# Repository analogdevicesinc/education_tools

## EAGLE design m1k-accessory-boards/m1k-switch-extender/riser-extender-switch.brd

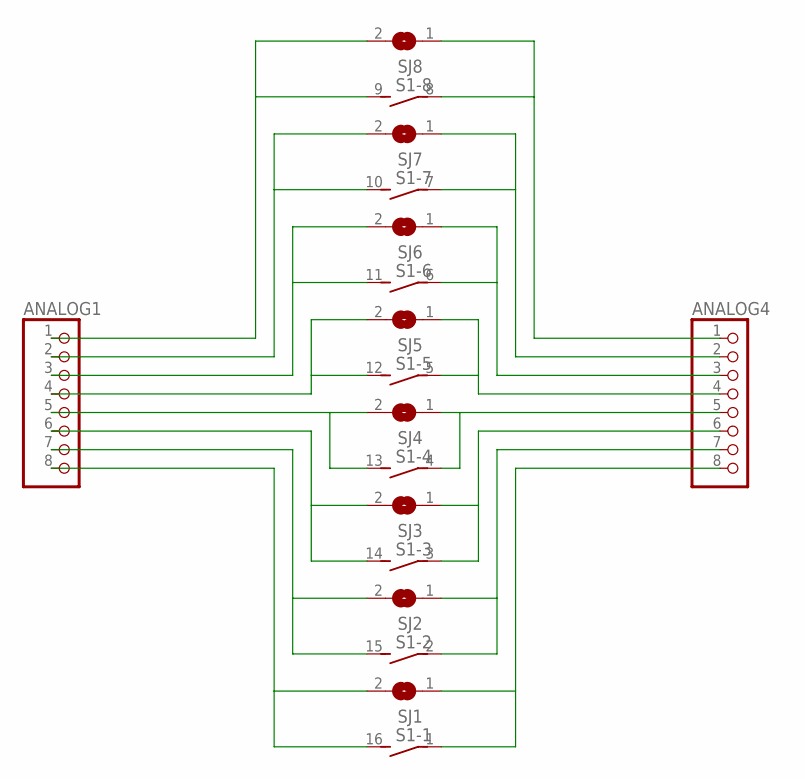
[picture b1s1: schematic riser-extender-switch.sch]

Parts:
ANALOG1, ANALOG4: PINHD-1X8; 1X08
S1: DIP08S
SJ1, SJ2, SJ3, SJ4, SJ5, SJ6, SJ7, SJ8: SJ

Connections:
unnamed: ANALOG1.1, S1.9 (2), SJ8.2
unnamed: ANALOG1.2, S1.10 (2), SJ7.2
unnamed: ANALOG1.3, S1.11 (2), SJ6.2
unnamed: ANALOG1.4, S1.12 (2), SJ5.2
unnamed: ANALOG1.5, S1.13 (2), SJ4.2
unnamed: ANALOG1.6, S1.14 (2), SJ3.2
unnamed: ANALOG1.7, S1.15 (2), SJ2.2
unnamed: ANALOG1.8, S1.16 (2), SJ1.2
unnamed: ANALOG4.5, S1.4 (1), SJ4.1
unnamed: ANALOG4.6, S1.3 (1), SJ3.1
unnamed: ANALOG4.7, S1.2 (1), SJ2.1
unnamed: ANALOG4.8, S1.1, SJ1.1
unnamed: ANALOG4.4, S1.5 (1), SJ5.1
unnamed: ANALOG4.3, S1.6 (1), SJ6.1
unnamed: ANALOG4.2, S1.7 (1), SJ7.1
unnamed: ANALOG4.1, S1.8 (1), SJ8.1

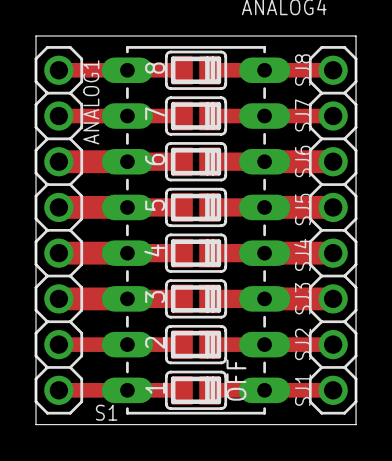
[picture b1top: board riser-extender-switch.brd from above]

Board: 2 copper layers, 17.8 x 21.6 mm, 11 parts (0 on the bottom side), 16 nets.

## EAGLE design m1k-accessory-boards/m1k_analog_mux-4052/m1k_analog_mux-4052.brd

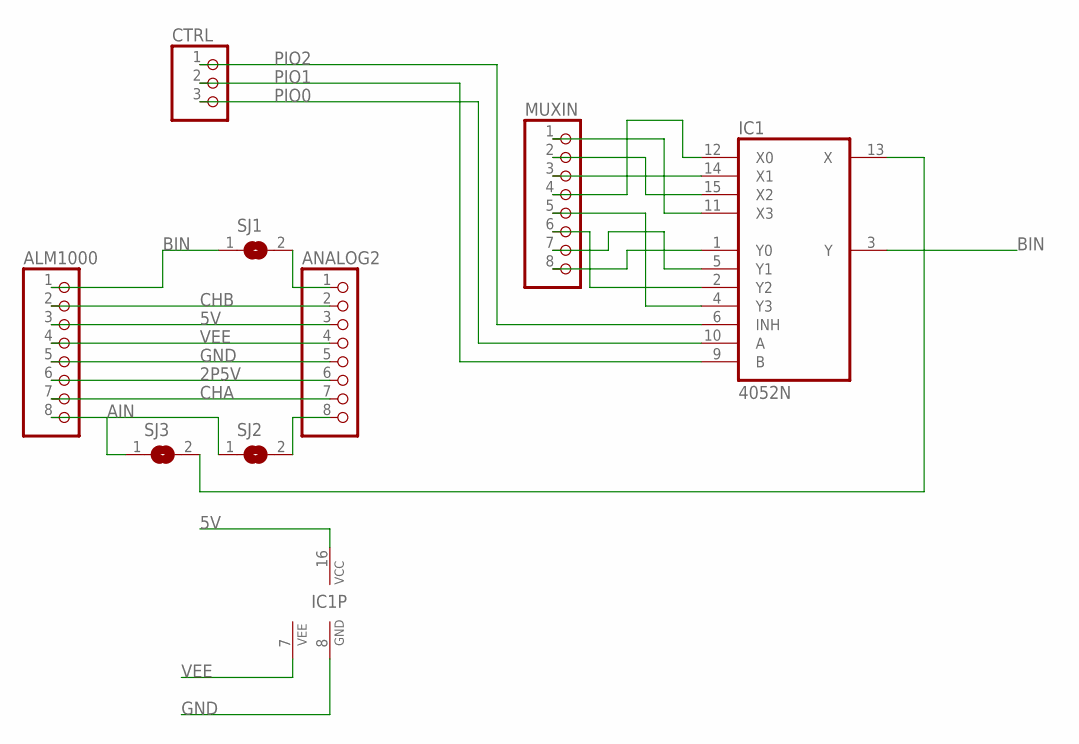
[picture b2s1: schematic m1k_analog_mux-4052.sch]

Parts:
ALM1000: PINHD-1X8; 1X08
ANALOG2: PINHD-1X8; 1X08
CTRL: PINHD-1X3; 1X03
IC1: 4052N; DIL16
MUXIN: PINHD-1X8; 1X08
SJ1, SJ2, SJ3: SJ

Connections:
2P5V: ALM1000.6, ANALOG2.6
5V: ALM1000.3, ANALOG2.3, IC1.16 (VCC)
AIN: ALM1000.8, SJ2.1, SJ3.1
BIN: ALM1000.1, IC1.3 (Y), SJ1.1
CHA: ALM1000.7, ANALOG2.7
CHB: ALM1000.2, ANALOG2.2
GND: ALM1000.5, ANALOG2.5, IC1.8 (GND)
unnamed: IC1.1 (Y0), MUXIN.8
unnamed: ANALOG2.1, SJ1.2
unnamed: IC1.5 (Y1), MUXIN.7
unnamed: IC1.2 (Y2), MUXIN.6
unnamed: IC1.4 (Y3), MUXIN.5
unnamed: IC1.11 (X3), MUXIN.1
unnamed: IC1.15 (X2), MUXIN.2
unnamed: IC1.14 (X1), MUXIN.3
unnamed: IC1.12 (X0), MUXIN.4
unnamed: ANALOG2.8, SJ2.2
unnamed: IC1.13 (X), SJ3.2
PIO0: CTRL.3, IC1.10 (A)
PIO1: CTRL.2, IC1.9 (B)
PIO2: CTRL.1, IC1.6 (INH)
VEE: ALM1000.4, ANALOG2.4, IC1.7 (VEE)

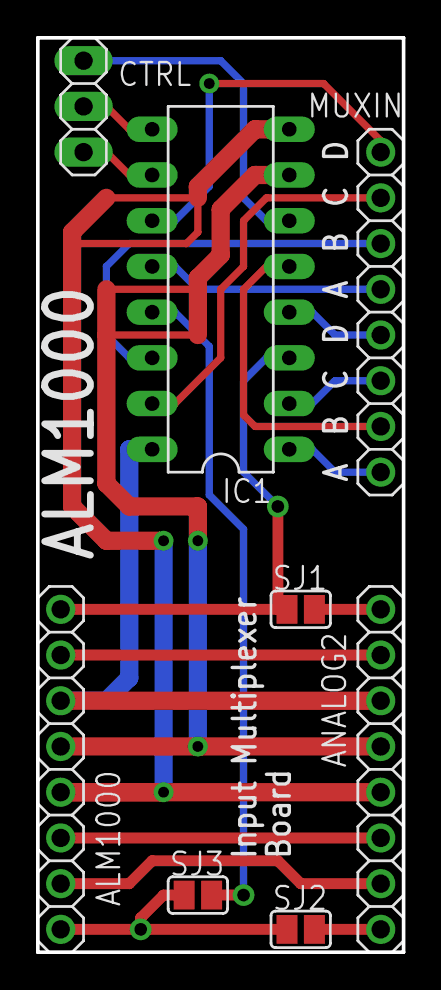
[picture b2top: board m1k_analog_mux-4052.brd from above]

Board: 2 copper layers, 20.3 x 50.8 mm, 8 parts (0 on the bottom side), 22 nets.

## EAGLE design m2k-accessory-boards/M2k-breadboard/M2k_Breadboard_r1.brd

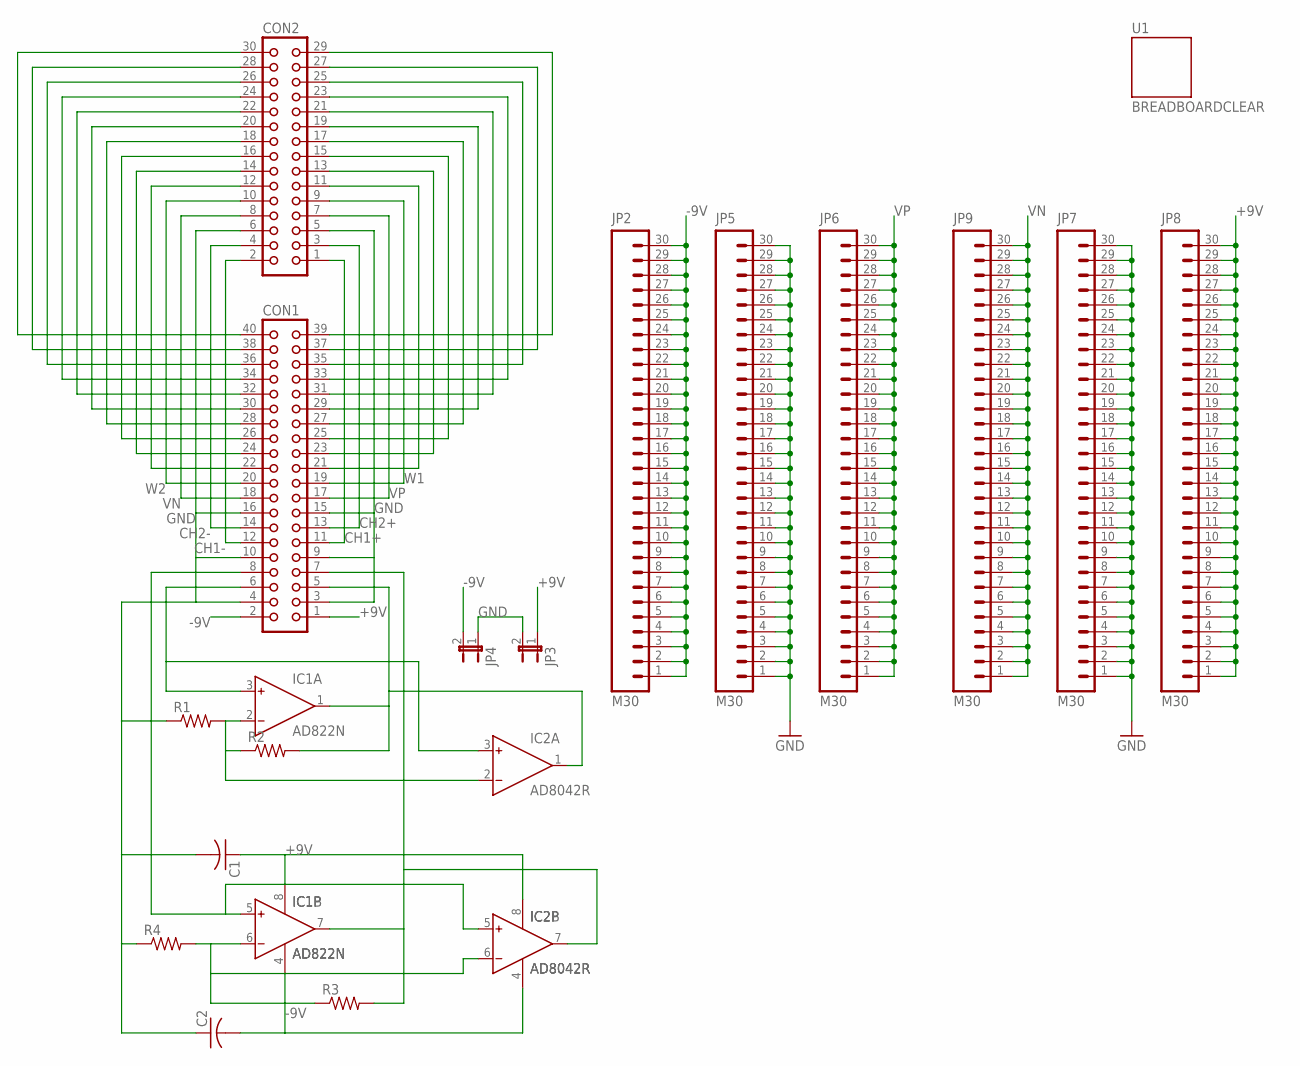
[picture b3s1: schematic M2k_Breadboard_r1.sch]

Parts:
C1, C2: C-US050-024X044; C050-024X044
CON1: CON40
CON2: CON34
IC1: AD822N; DIL08
IC2: AD8042R; SO8
JP2, JP5, JP6, JP7, JP8, JP9: M30; 1X30
JP3, JP4: JP1E; JP1
R1, R2, R3, R4: R-US_0207/7; 0207/7
U1: BREADBOARDCLEAR; BREADBOARD_CLEAR

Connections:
+9V: C1.1, CON1.1, IC1.8 (V+), IC2.8 (V+), JP3.1, JP8.1, JP8.2, JP8.3, JP8.4, JP8.5, JP8.6, JP8.7, JP8.8, JP8.9, JP8.10, JP8.11, JP8.12, JP8.13, JP8.14, JP8.15, JP8.16, JP8.17, JP8.18, JP8.19, JP8.20, JP8.21, JP8.22, JP8.23, JP8.24, JP8.25, JP8.26, JP8.27, JP8.28, JP8.29, JP8.30
-9V: C2.2, CON1.2, IC1.4 (V-), IC2.4 (V-), JP2.1, JP2.2, JP2.3, JP2.4, JP2.5, JP2.6, JP2.7, JP2.8, JP2.9, JP2.10, JP2.11, JP2.12, JP2.13, JP2.14, JP2.15, JP2.16, JP2.17, JP2.18, JP2.19, JP2.20, JP2.21, JP2.22, JP2.23, JP2.24, JP2.25, JP2.26, JP2.27, JP2.28, JP2.29, JP2.30, JP4.2
CH1+: CON1.11, CON2.1
CH1-: CON1.12, CON2.2
CH2+: CON1.13, CON2.3
CH2-: CON1.14, CON2.4
GND: C1.2, C2.1, CON1.3, CON1.4, CON1.9, CON1.10, CON1.15, CON1.16, CON2.5, CON2.6, JP3.2, JP4.1, JP5.1, JP5.2, JP5.3, JP5.4, JP5.5, JP5.6, JP5.7, JP5.8, JP5.9, JP5.10, JP5.11, JP5.12, JP5.13, JP5.14, JP5.15, JP5.16, JP5.17, JP5.18, JP5.19, JP5.20, JP5.21, JP5.22, JP5.23, JP5.24, JP5.25, JP5.26, JP5.27, JP5.28, JP5.29, JP5.30, JP7.1, JP7.2, JP7.3, JP7.4, JP7.5, JP7.6, JP7.7, JP7.8, JP7.9, JP7.10, JP7.11, JP7.12, JP7.13, JP7.14, JP7.15, JP7.16, JP7.17, JP7.18, JP7.19, JP7.20, JP7.21, JP7.22, JP7.23, JP7.24, JP7.25, JP7.26, JP7.27, JP7.28, JP7.29, JP7.30, R1.1, R4.1
unnamed: CON1.5, IC1.1 (OUT), IC2.1 (OUT), R2.2
unnamed: CON1.6, IC1.3 (IN+), IC2.3 (IN+)
unnamed: CON1.8, IC1.5 (IN+), IC2.5 (IN+)
unnamed: CON1.7, IC1.7 (OUT), IC2.7 (OUT), R3.2
unnamed: IC1.6 (IN-), IC2.6 (IN-), R3.1, R4.2
unnamed: CON1.21, CON2.11
unnamed: CON1.23, CON2.13
unnamed: CON1.25, CON2.15
unnamed: CON1.27, CON2.17
unnamed: CON1.29, CON2.19
unnamed: CON1.31, CON2.21
unnamed: CON1.33, CON2.23
unnamed: CON1.35, CON2.25
unnamed: CON1.37, CON2.27
unnamed: CON1.39, CON2.29
unnamed: IC1.2 (IN-), IC2.2 (IN-), R1.2, R2.1
unnamed: CON1.22, CON2.12
unnamed: CON1.24, CON2.14
unnamed: CON1.26, CON2.16
unnamed: CON1.28, CON2.18
unnamed: CON1.30, CON2.20
unnamed: CON1.32, CON2.22
unnamed: CON1.34, CON2.24
unnamed: CON1.36, CON2.26
unnamed: CON1.38, CON2.28
unnamed: CON1.40, CON2.30
VN: CON1.18, CON2.8, JP9.1, JP9.2, JP9.3, JP9.4, JP9.5, JP9.6, JP9.7, JP9.8, JP9.9, JP9.10, JP9.11, JP9.12, JP9.13, JP9.14, JP9.15, JP9.16, JP9.17, JP9.18, JP9.19, JP9.20, JP9.21, JP9.22, JP9.23, JP9.24, JP9.25, JP9.26, JP9.27, JP9.28, JP9.29, JP9.30
VP: CON1.17, CON2.7, JP6.1, JP6.2, JP6.3, JP6.4, JP6.5, JP6.6, JP6.7, JP6.8, JP6.9, JP6.10, JP6.11, JP6.12, JP6.13, JP6.14, JP6.15, JP6.16, JP6.17, JP6.18, JP6.19, JP6.20, JP6.21, JP6.22, JP6.23, JP6.24, JP6.25, JP6.26, JP6.27, JP6.28, JP6.29, JP6.30
W1: CON1.19, CON2.9
W2: CON1.20, CON2.10

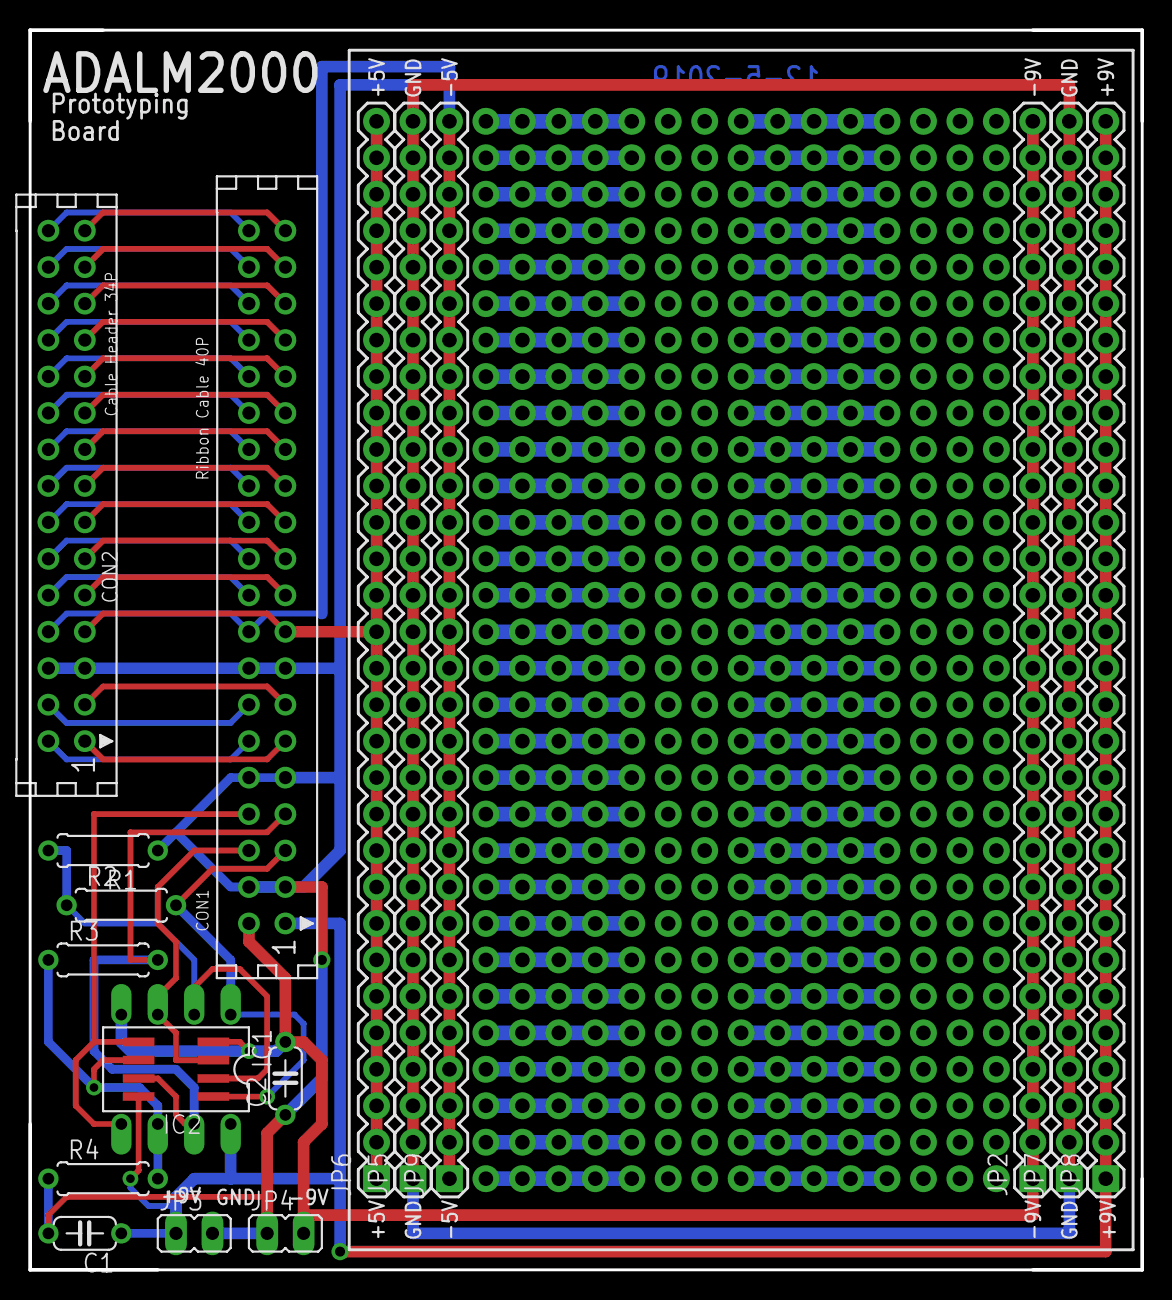
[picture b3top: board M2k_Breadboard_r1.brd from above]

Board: 2 copper layers, 77.5 x 86.4 mm, 19 parts (0 on the bottom side), 37 nets.

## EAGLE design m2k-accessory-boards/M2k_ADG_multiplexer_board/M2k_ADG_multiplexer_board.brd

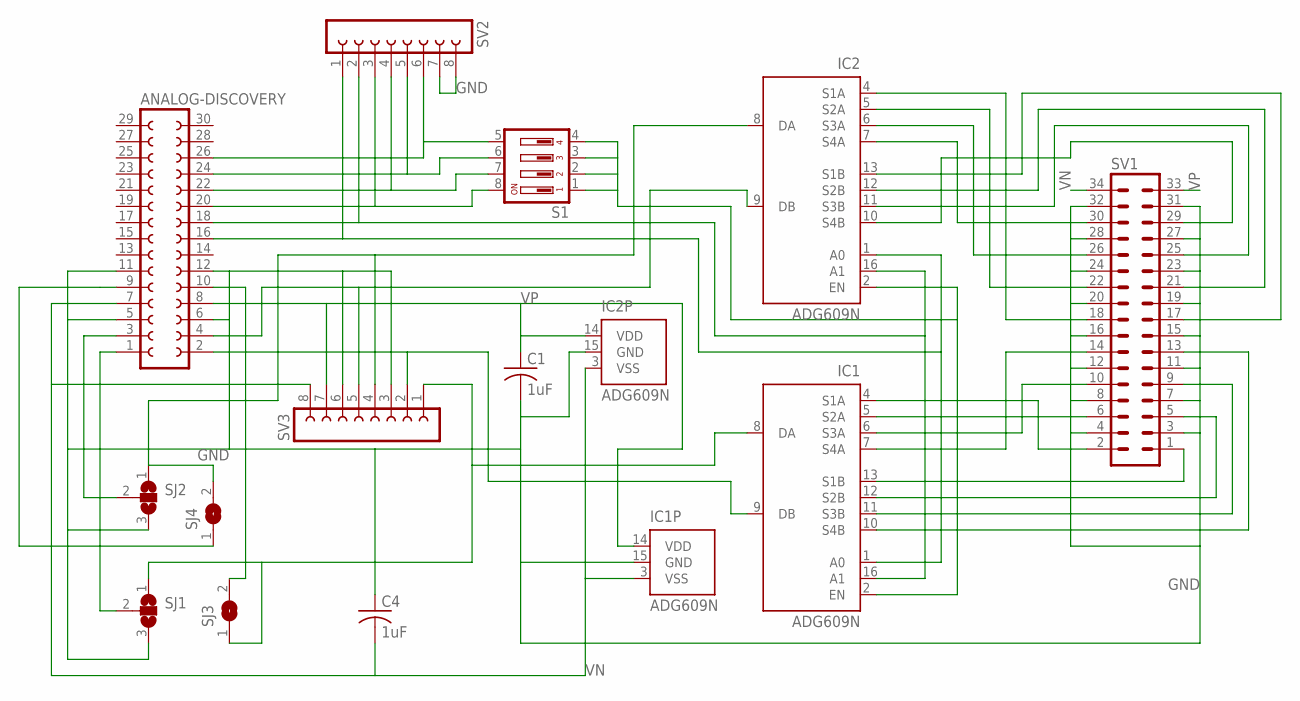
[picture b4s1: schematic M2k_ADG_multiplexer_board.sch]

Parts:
ANALOG-DISCOVERY: FE15-2
C1, C4: 1uF; C050-024X044
IC1, IC2: ADG609N; DIL16
S1: DIP04YL
SJ1, SJ2: SJ2W; SJ_2
SJ3, SJ4: SJ
SV1: MA17-2
SV2, SV3: FE08-1; FE08

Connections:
ES: IC1.8 (DA), SJ1.1, SJ3.1, SV3.1
GND: ANALOG-DISCOVERY.5, ANALOG-DISCOVERY.6, ANALOG-DISCOVERY.11, ANALOG-DISCOVERY.12, C1.2, C4.1, IC1.15 (GND), IC2.15 (GND), SJ1.3, SJ2.3, SV1.3, SV1.4, SV1.7, SV1.8, SV1.11, SV1.12, SV1.15, SV1.16, SV1.19, SV1.20, SV1.23, SV1.24, SV1.27, SV1.28, SV1.31, SV1.32, SV2.7, SV2.8, SV3.3, SV3.6
unnamed: ANALOG-DISCOVERY.26, S1.5, SV2.6
unnamed: IC1.4 (S1A), SV1.2
unnamed: IC1.2 (EN), IC2.2 (EN), S1.1, S1.2, S1.3, S1.4
unnamed: ANALOG-DISCOVERY.2, IC1.9 (DB), SV3.2
unnamed: IC1.13 (S1B), SV1.1
unnamed: IC1.5 (S2A), SV1.6
unnamed: IC2.8 (DA), SJ2.1, SJ4.2, SV3.4
unnamed: IC1.12 (S2B), SV1.5
unnamed: IC1.6 (S3A), SV1.10
unnamed: ANALOG-DISCOVERY.4, IC2.9 (DB), SV3.5
unnamed: ANALOG-DISCOVERY.16, IC1.1 (A0), IC2.1 (A0), SV2.1
unnamed: ANALOG-DISCOVERY.18, IC1.16 (A1), IC2.16 (A1), SV2.2
unnamed: IC1.7 (S4A), SV1.14
unnamed: IC1.11 (S3B), SV1.9
unnamed: IC1.10 (S4B), SV1.13
unnamed: IC2.4 (S1A), SV1.18
unnamed: IC2.5 (S2A), SV1.22
unnamed: IC2.6 (S3A), SV1.26
unnamed: IC2.7 (S4A), SV1.30
unnamed: IC2.13 (S1B), SV1.17
unnamed: IC2.12 (S2B), SV1.21
unnamed: IC2.11 (S3B), SV1.25
unnamed: IC2.10 (S4B), SV1.29
unnamed: ANALOG-DISCOVERY.1, SJ1.2
unnamed: ANALOG-DISCOVERY.3, SJ2.2
unnamed: ANALOG-DISCOVERY.20, S1.8, SV2.3
unnamed: ANALOG-DISCOVERY.22, S1.7, SV2.4
unnamed: ANALOG-DISCOVERY.24, S1.6, SV2.5
VN: ANALOG-DISCOVERY.7, C4.2, IC1.3 (VSS), IC2.3 (VSS), SV1.34, SV3.8
VP: ANALOG-DISCOVERY.8, C1.1, IC1.14 (VDD), IC2.14 (VDD), SV1.33, SV3.7
W1: ANALOG-DISCOVERY.10, SJ3.2
W2: ANALOG-DISCOVERY.9, SJ4.1

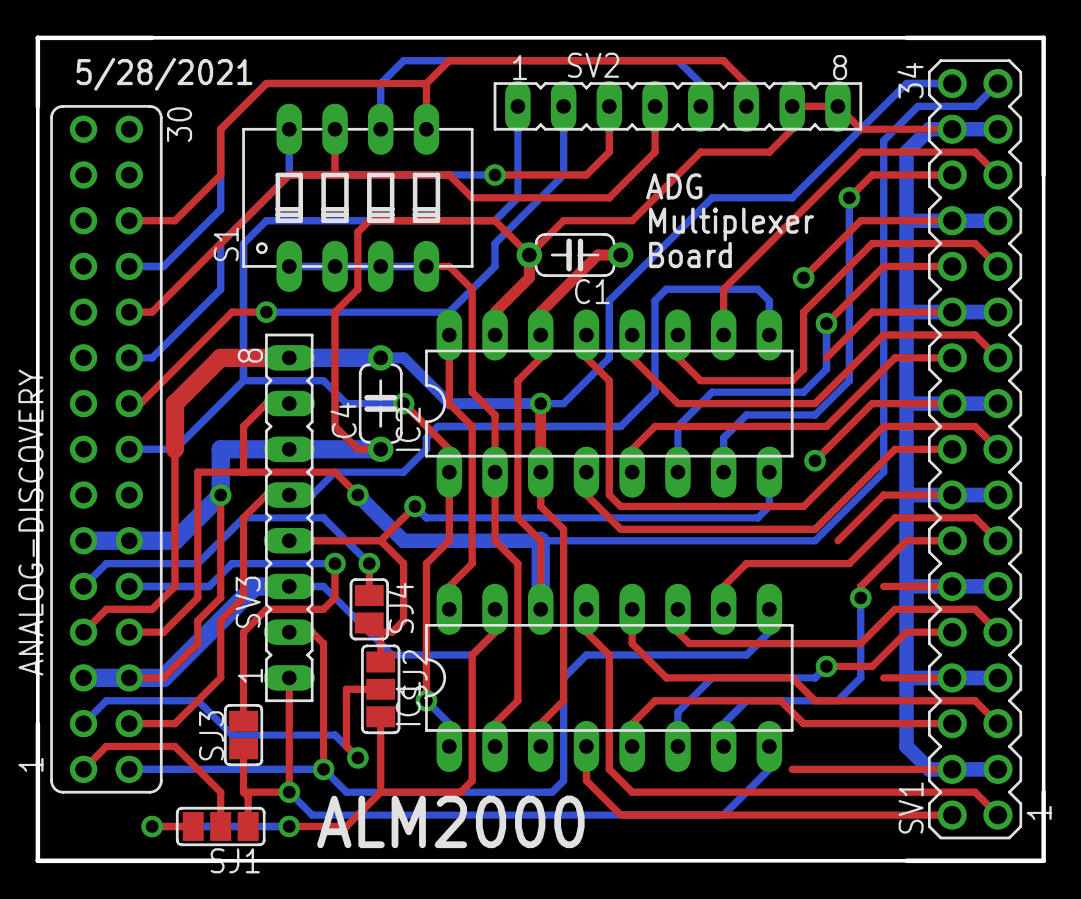
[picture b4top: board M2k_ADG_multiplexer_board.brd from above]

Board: 2 copper layers, 55.9 x 45.7 mm, 13 parts (0 on the bottom side), 34 nets.
